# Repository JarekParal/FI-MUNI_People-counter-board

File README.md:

# FI-MUNI_People-counter-board

[Czech documentation](./DOCUMENTATION-CZ.md)

Simple board with LED displays, decade counter, BCD to 7-segment decoder

## Simulation of circuit in Every Circuit:
- [first simulation (just one counter in circuit)](http://everycircuit.com/circuit/5534090356064256)
- [second simulation (two counters in circuit)](http://everycircuit.com/circuit/5164988449947648)

## Parts
- 4× 74LS90 - Decadic BCD counter ([datasheet](http://www.ti.com/lit/ds/symlink/sn74ls90.pdf)) - can be purchased [MyArduino.cz](https://www.myarduino.cz/logicke-obvody-74ls90-dekadicky-bcd-citac) or [Farnell.com](http://cz.farnell.com/texas-instruments/sn74ls90n/ic-counter-multiplier-divider/dp/1470790?st=74ls90)
- 4× 74LS47 - Decoder BCD/7segm. ([datasheet](http://www.ti.com/lit/ds/symlink/sn74ls47.pdf)) - can be purchased [MyArduino.cz](https://www.myarduino.cz/logicke-obvody-74ls47-dekoder-z-bcd-na-7-segmentovy-kod-s-otevrenym-kolektorem) or [Farnell.com](http://cz.farnell.com/texas-instruments/sn74ls90n/ic-counter-multiplier-divider/dp/1470790?st=74ls90)
- 4× 7 seg. display HD-A554RD ([datasheet](https://www.gme.cz/data/attachments/dsh.512-182.1.pdf)) - can be purchased [GME](https://www.gme.cz/led-display-14-2mm-red-hd-a554rd)
- 31× resistor 220 Ω v package SMD0603
- 1× resistor 10 kΩ v package SMD0603
- 2×2 a 2×4 90 degree pinheads 2,54 mm
- 1× MicroUSB connector - can be purchased [Mouser](https://cz.mouser.com/ProductDetail/Molex/47346-0001?qs=%2fha2pyFadugJe2m2PwsxZF%2fSs5SLGnHK0WVEsekv2hnqwx5TiE8qVw%3d%3d) or Farnell

## Parameters
- power supply: 5 V over pinheads or microUSB connector
- consumption: approx. 200 mA 
- size of PCB: 70 × 69 mm

## Versions of PCB - bugs and modification
### v1.0
- wrong value of the capacitor C2 near IC 555: 10 uF -> 200 nF
- wrong net to the potentiometer R29 -> delete this net in v1.1 or modify the R29 (cut off one pin on R29)
### v1.1
- fix bugs from v1.0

## Photos 

PCB with all parts

PCB in operation

PCB with USB power supply and PIR sensor

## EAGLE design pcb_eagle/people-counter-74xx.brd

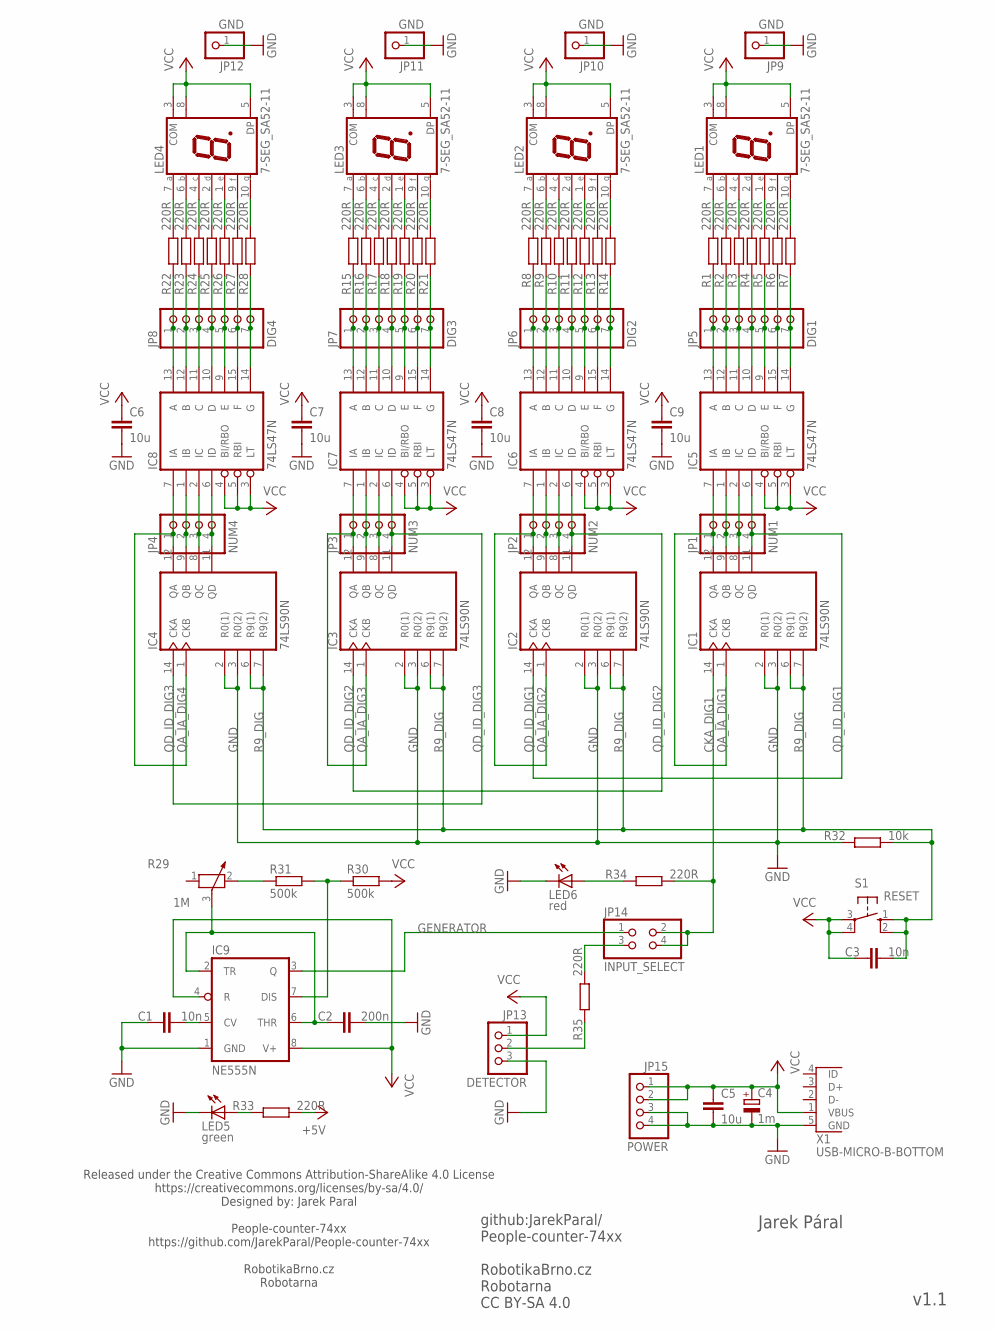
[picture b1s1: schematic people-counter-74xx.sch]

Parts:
C1, C3: 10n; C0603
C2: 200n; C0805
C4: 1m; E5-10,5
C5, C6, C7, C8, C9: 10u; C0805
IC1, IC2, IC3, IC4: 74LS90N; DIL14
IC5, IC6, IC7, IC8: 74LS47N; DIL16
IC9: NE555N; DIL08
JP1: NUM1; 1X04
JP2: NUM2; 1X04
JP3: NUM3; 1X04
JP4: NUM4; 1X04
JP5: DIG1; 1X07
JP6: DIG2; 1X07
JP7: DIG3; 1X07
JP8: DIG4; 1X07
JP9, JP10, JP11, JP12: GND; 1X01
JP13: DETECTOR; 1X03/90
JP14: INPUT_SELECT; 2X02
JP15: POWER; 1X04/90
LED1, LED2, LED3, LED4: 7-SEG_SA52-11; SA52-11
LED5: green; CHIPLED_0603
LED6: red; CHIPLED_0603
R1, R2, R3, R4, R5, R6, R7, R8, R9, R10, R11, R12, R13, R14, R15, R16, R17, R18, R19, R20, R21, R22, R23, R24, R25, R26, R27, R28, R33, R34, R35: 220R; R0603
R29: 1M; PT-10
R30, R31: 500k; R0603
R32: 10k; R0603
S1: RESET; B3F-10XX
X1: USB-MICRO-B-BOTTOM; USB-MICRO-B-BOTTOM-MOLEX

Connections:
+5V: R33.2
A_DIG1: IC5.13 (A), JP5.1, R1.1
A_DIG2: IC6.13 (A), JP6.1, R8.1
A_DIG3: IC7.13 (A), JP7.1, R15.1
A_DIG4: IC8.13 (A), JP8.1, R22.1
A_DIG_1: LED1.7 (A), R1.2
A_DIG_2: LED2.7 (A), R8.2
A_DIG_3: LED3.7 (A), R15.2
A_DIG_4: LED4.7 (A), R22.2
B_DIG1: IC5.12 (B), JP5.2, R2.1
B_DIG2: IC6.12 (B), JP6.2, R9.1
B_DIG3: IC7.12 (B), JP7.2, R16.1
B_DIG4: IC8.12 (B), JP8.2, R23.1
B_DIG_1: LED1.6 (B), R2.2
B_DIG_2: LED2.6 (B), R9.2
B_DIG_3: LED3.6 (B), R16.2
B_DIG_4: LED4.6 (B), R23.2
CKA_DIG1: IC1.14 (CKA), JP14.2, JP14.4, R34.2
C_DIG1: IC5.11 (C), JP5.3, R3.1
C_DIG2: IC6.11 (C), JP6.3, R10.1
C_DIG3: IC7.11 (C), JP7.3, R17.1
C_DIG4: IC8.11 (C), JP8.3, R24.1
C_DIG_1: LED1.4 (C), R3.2
C_DIG_2: LED2.4 (C), R10.2
C_DIG_3: LED3.4 (C), R17.2
C_DIG_4: LED4.4 (C), R24.2
D_DIG1: IC5.10 (D), JP5.4, R4.1
D_DIG2: IC6.10 (D), JP6.4, R11.1
D_DIG3: IC7.10 (D), JP7.4, R18.1
D_DIG4: IC8.10 (D), JP8.4, R25.1
D_DIG_1: LED1.2 (D), R4.2
D_DIG_2: LED2.2 (D), R11.2
D_DIG_3: LED3.2 (D), R18.2
D_DIG_4: LED4.2 (D), R25.2
E_DIG1: IC5.9 (E), JP5.5, R5.1
E_DIG2: IC6.9 (E), JP6.5, R12.1
E_DIG3: IC7.9 (E), JP7.5, R19.1
E_DIG4: IC8.9 (E), JP8.5, R26.1
E_DIG_1: LED1.1 (E), R5.2
E_DIG_2: LED2.1 (E), R12.2
E_DIG_3: LED3.1 (E), R19.2
E_DIG_4: LED4.1 (E), R26.2
F_DIG1: IC5.15 (F), JP5.6, R6.1
F_DIG2: IC6.15 (F), JP6.6, R13.1
F_DIG3: IC7.15 (F), JP7.6, R20.1
F_DIG4: IC8.15 (F), JP8.6, R27.1
F_DIG_1: LED1.9 (F), R6.2
F_DIG_2: LED2.9 (F), R13.2
F_DIG_3: LED3.9 (F), R20.2
F_DIG_4: LED4.9 (F), R27.2
GENERATOR: IC9.3 (Q), JP14.1
GND: C1.1, C2.2, C4.-, C5.2, C6.2, C7.2, C8.2, C9.2, IC1.2 (R0(1)), IC1.3 (R0(2)), IC1.10 (GND), IC2.2 (R0(1)), IC2.3 (R0(2)), IC2.10 (GND), IC3.2 (R0(1)), IC3.3 (R0(2)), IC3.10 (GND), IC4.2 (R0(1)), IC4.3 (R0(2)), IC4.10 (GND), IC5.8 (GND), IC6.8 (GND), IC7.8 (GND), IC8.8 (GND), IC9.1 (GND), JP9.1, JP10.1, JP11.1, JP12.1, JP13.3, JP15.3, JP15.4, LED5.C, LED6.C, R32.1, X1.5 (GND)
G_DIG1: IC5.14 (G), JP5.7, R7.1
G_DIG2: IC6.14 (G), JP6.7, R14.1
G_DIG3: IC7.14 (G), JP7.7, R21.1
G_DIG4: IC8.14 (G), JP8.7, R28.1
G_DIG_1: LED1.10 (G), R7.2
G_DIG_2: LED2.10 (G), R14.2
G_DIG_3: LED3.10 (G), R21.2
G_DIG_4: LED4.10 (G), R28.2
unnamed: LED6.A, R34.1
unnamed: R29.2, R31.1
unnamed: C2.1, IC9.2 (TR), IC9.6 (THR), R29.3
unnamed: C1.2, IC9.5 (CV)
unnamed: IC9.7 (DIS), R30.1, R31.2
unnamed: LED5.A, R33.1
QA_IA_DIG1: IC1.1 (CKB), IC1.12 (QA), IC5.7 (IA), JP1.1
QA_IA_DIG2: IC2.1 (CKB), IC2.12 (QA), IC6.7 (IA), JP2.1
QA_IA_DIG3: IC3.1 (CKB), IC3.12 (QA), IC7.7 (IA), JP3.1
QA_IA_DIG4: IC4.1 (CKB), IC4.12 (QA), IC8.7 (IA), JP4.1
QB_IB_DIG1: IC1.9 (QB), IC5.1 (IB), JP1.2
QB_IB_DIG2: IC2.9 (QB), IC6.1 (IB), JP2.2
QB_IB_DIG3: IC3.9 (QB), IC7.1 (IB), JP3.2
QB_IB_DIG4: IC4.9 (QB), IC8.1 (IB), JP4.2
QC_IC_DIG1: IC1.8 (QC), IC5.2 (IC), JP1.3
QC_IC_DIG2: IC2.8 (QC), IC6.2 (IC), JP2.3
QC_IC_DIG3: IC3.8 (QC), IC7.2 (IC), JP3.3
QC_IC_DIG4: IC4.8 (QC), IC8.2 (IC), JP4.3
QD_ID_DIG1: IC1.11 (QD), IC2.14 (CKA), IC5.6 (ID), JP1.4
QD_ID_DIG2: IC2.11 (QD), IC3.14 (CKA), IC6.6 (ID), JP2.4
QD_ID_DIG3: IC3.11 (QD), IC4.14 (CKA), IC7.6 (ID), JP3.4
QD_ID_DIG4: IC4.11 (QD), IC8.6 (ID), JP4.4
R9_DIG: C3.2, IC1.6 (R9(1)), IC1.7 (R9(2)), IC2.6 (R9(1)), IC2.7 (R9(2)), IC3.6 (R9(1)), IC3.7 (R9(2)), IC4.6 (R9(1)), IC4.7 (R9(2)), R32.2, S1.1 (S), S1.2 (S1)
SIGNAL_INPUT: JP13.2, R35.1
SIGNAL_INPUT_: JP14.3, R35.2
VCC: C3.1, C4.+, C5.1, C6.1, C7.1, C8.1, C9.1, IC1.5 (VCC), IC2.5 (VCC), IC3.5 (VCC), IC4.5 (VCC), IC5.3 (LT), IC5.4 (BI/RBO), IC5.5 (RBI), IC5.16 (VCC), IC6.3 (LT), IC6.4 (BI/RBO), IC6.5 (RBI), IC6.16 (VCC), IC7.3 (LT), IC7.4 (BI/RBO), IC7.5 (RBI), IC7.16 (VCC), IC8.3 (LT), IC8.4 (BI/RBO), IC8.5 (RBI), IC8.16 (VCC), IC9.4 (R), IC9.8 (V+), JP13.1, JP15.1, JP15.2, LED1.3 (COM), LED1.5 (DP), LED1.8 (COM), LED2.3 (COM), LED2.5 (DP), LED2.8 (COM), LED3.3 (COM), LED3.5 (DP), LED3.8 (COM), LED4.3 (COM), LED4.5 (DP), LED4.8 (COM), R30.2, S1.3, S1.4 (P1), X1.1 (VBUS)

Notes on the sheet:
github:JarekParal/ People-counter-74xx RobotikaBrno.cz Robotarna CC BY-SA 4.0
Jarek Páral
v1.1
Released under the Creative Commons Attribution-ShareAlike 4.0 License https://creativecommons.org/licenses/by-sa/4.0/ Designed by: Jarek Paral People-counter-74xx https://github.com/JarekParal/People-counter-74xx RobotikaBrno.cz Robotarna

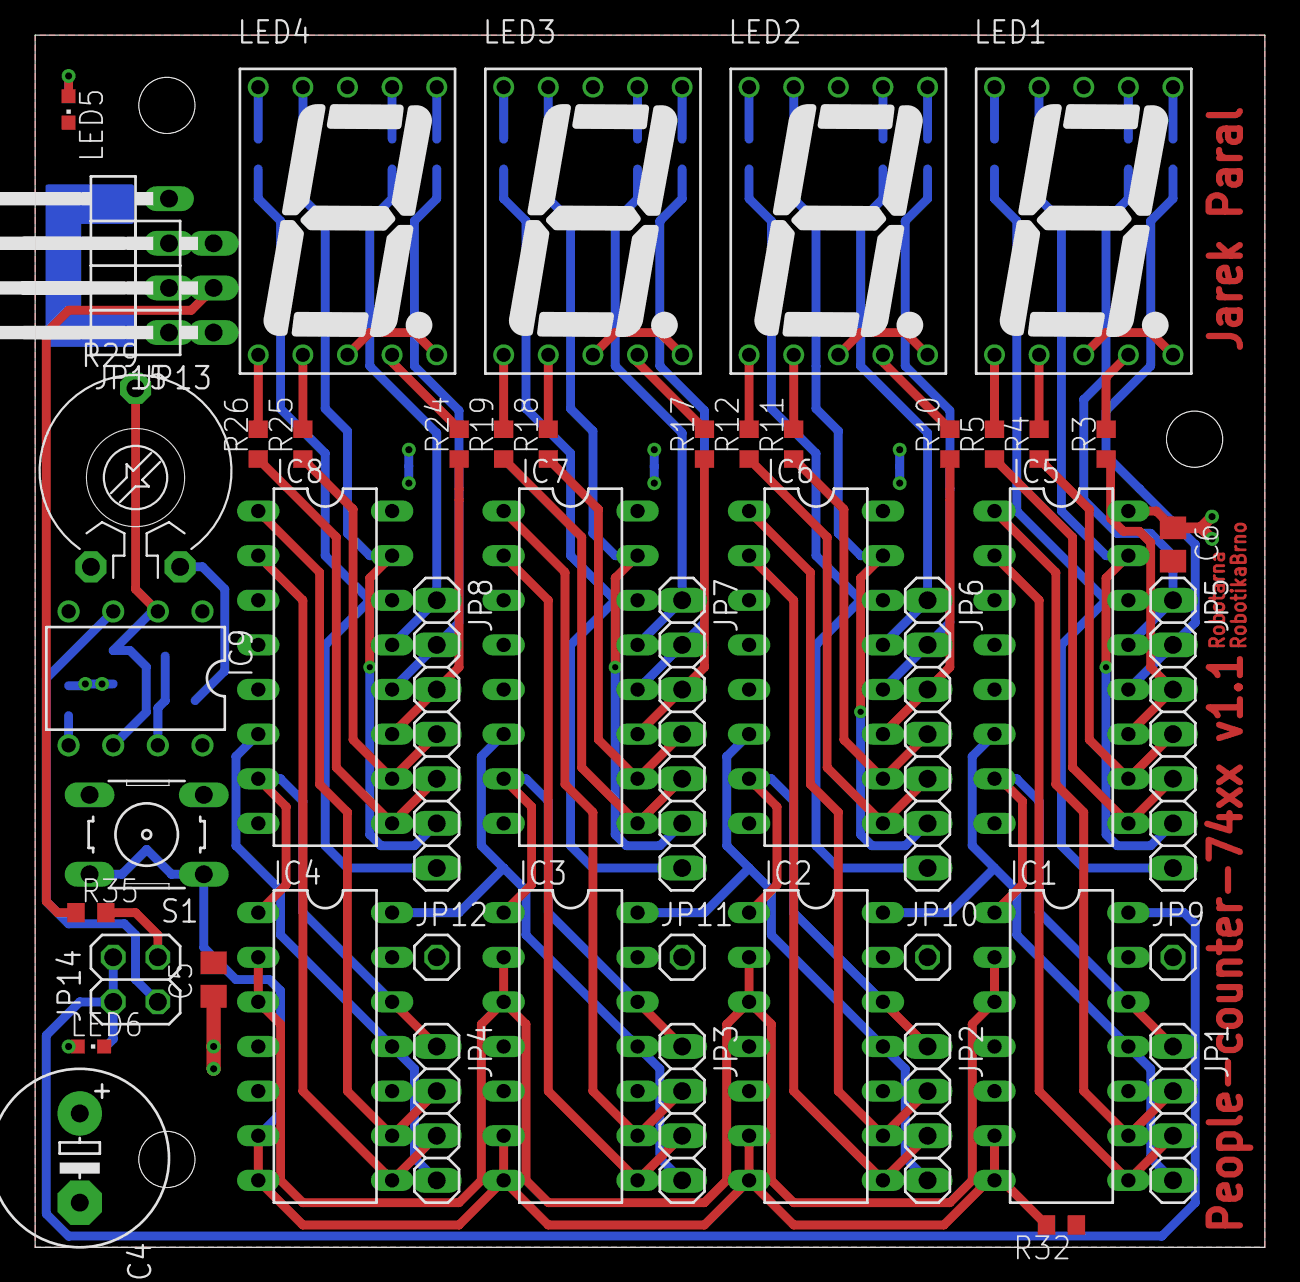
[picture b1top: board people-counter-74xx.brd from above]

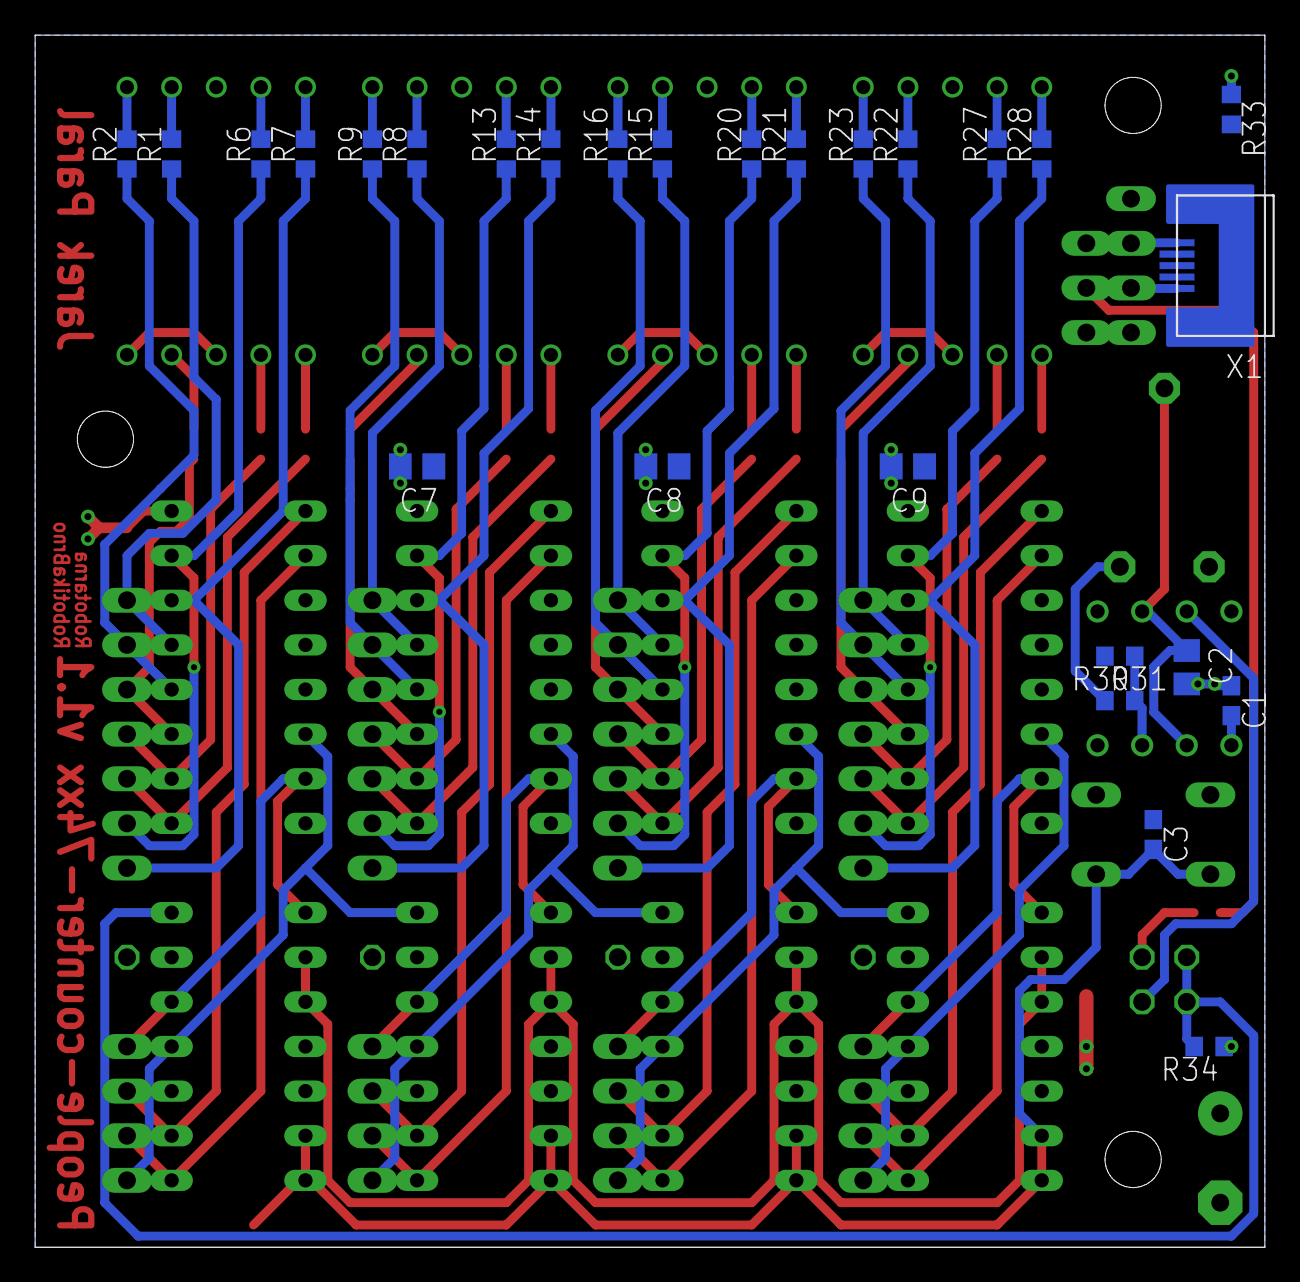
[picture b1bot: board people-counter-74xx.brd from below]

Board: 2 copper layers, 70.0 x 69.0 mm, 76 parts (27 on the bottom side), 85 nets.

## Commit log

2017-12-11 Schema: first version
2017-12-11 Update README and add BOM
2017-12-12 Grammar correction in README
2017-12-14 Schema: improves - remove excessive AND2 gate, add SW to reset counter IC
2018-01-29 Schema: final version of schema
2018-01-29 PCB: add footprint of part HD-A552RD
2018-01-29 PCB: rename folder "pcb" to "pcb_kicad"
2018-01-29 REPO: add Eagle .gitignore
2018-01-29 PCB_EAGLE: add first version of schema and layout of board with one LED segment (= design block)
2018-01-29 PCB_EAGLE: add design module - LED segment counter
2018-01-29 PCB_EAGLE: finish layout of 4 design module (LED segment counter}
2018-01-29 PCB_EAGLE: improve nets in design block LED segment counter
2018-01-30 PCB_EAGLE: add frequency square wave generator based on the NE555 and some connectors to schema
2018-01-31 PCB_EAGLE: final layout of board
2018-02-02 PCB_EAGLE: add a few description text and some optimization of net
2018-02-14 PCB_EAGLE: start work on version 1.1 - repair layer of texts Robotarna RobotikaBrno
2018-02-15 DOC: add documentation for v1.0
2018-02-15 Update DOCUMENTATION.md
    Jazyková korektura
2018-09-18 PCB_EAGLE: fix two bugs from v1.0 - change value of C2 (10u -> 200n) - delete one wire on potentiometer (R29)
2018-09-18 DOC: improve documentation
2018-09-20 DOC: improve documentation - add info about versions
